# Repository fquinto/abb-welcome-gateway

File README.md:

# abb-welcome-gateway

ESP32-S3 gateway that connects an **ABB-Welcome / Busch-Welcome** 2-wire door
intercom to **Home Assistant**: doorbell notifications, remote door opening and
diagnostics, powered directly from the intercom bus.

| Top | Bottom |
|---|---|
|  |  |

## Highlights

- **Bus-powered**: TPS5430 buck converter runs the board from the ~28 V bus.
- **ESP32-S3-WROOM-1** with the antenna at the board edge and a proper copper
  keep-out.
- **Clean bus front-end**: filtered tap, TVS + reverse-polarity protection,
  polyfuse, Schmitt-buffered RX and open-drain TX drivers.
- **Three separated ground islands** (power / digital / bus) stitched at a
  single star point, so switching and RF return currents stay out of the bus
  reference.
- **ESPHome firmware**: native Home Assistant integration, OTA updates,
  YAML-only configuration for the end user.

## Repository layout

| Path | Contents |
|---|---|
| [`hardware/kicad-v3/`](hardware/kicad-v3/) | **The board** (KiCad 9): fully routed 2-layer PCB, DRC-clean. Source of truth for the hardware. |
| [`firmware/esphome/`](firmware/esphome/) | ESPHome configuration + `abb_welcome` custom component. |
| [`docs/`](docs/) | [Status](docs/STATUS.md) · [Pending tasks](docs/TODO.md) · [User guide](docs/user-guide.md). |
| [`legacy/`](legacy/) | Frozen design history: original EasyEDA v2 design, the tscircuit schematic capture of v3 and the conversion tooling. |

## Status

- **Hardware**: v3.0 design finished and fully routed; pre-fabrication
  verification pending (details in [docs/STATUS.md](docs/STATUS.md)).
- **Firmware**: ESPHome skeleton in place; ABB-Welcome bus protocol in
  development ([docs/TODO.md](docs/TODO.md)).

## Getting started

See the [user guide](docs/user-guide.md) for wiring, first flash over the
FTDI header and Home Assistant setup.

For hardware development: open `hardware/kicad-v3/abb-welcome-gateway-v3.kicad_pro`
in KiCad 9. Design rules, net classes and the ground-island scheme are described
in [`hardware/kicad-v3/README.md`](hardware/kicad-v3/README.md).

## Community & discussion

Questions, ideas or want to share your build? Join the discussion on Telegram:

## Donations for software development

If this project is useful to you, you can support its development:

Thank you for collaborating and helping the development of software improvements.

## Credits & license

The hardware derives from the original bus interface design by **mat931**.
Hardware is licensed under **CERN-OHL-W v2** (see [`LICENSE`](LICENSE));
the full design history is preserved in [`legacy/`](legacy/) and in the git log.

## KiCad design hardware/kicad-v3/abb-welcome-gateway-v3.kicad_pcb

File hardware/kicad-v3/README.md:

# KiCad v3 — routing target

KiCad project exported from the tscircuit v3 design (`legacy/tscircuit/index.circuit.tsx`)
so the board can be **routed in KiCad** (tscircuit's autorouter does not converge
on this board and produces no copper pours, which this design needs — three GND
islands, an RF module, the buck power stage and the 28 V bus all want planes /
poured copper, not point-to-point traces).

## Files

- `abb-welcome-gateway-v3.kicad_pro` — project (open this in KiCad).
- `abb-welcome-gateway-v3.kicad_pcb` — board: **fully routed** (traces, vias,
  the three GND island pours and stitching). `kicad-cli pcb drc`: 0 errors,
  0 unconnected items.
- `abb-welcome-gateway-v3.kicad_sch` — schematic.

Generated with `circuit-json-to-kicad` (KiCad file format `20241229`, i.e. KiCad 8/9).

## Source-of-truth note

Routing has started (and finished) here, so **this KiCad project is now the
source of truth for the PCB**. The tscircuit side (`legacy/tscircuit/index.circuit.tsx`)
is frozen as schematic reference; it does NOT reflect the physical changes below.

### Divergences from the tscircuit source (v3.0 routed)

- **U2 footprint replaced**: the tscircuit wrapper's hand-made 61-pad QFN-style
  footprint is not the real module. U2 now uses KiCad's official
  `RF_Module:ESP32-S3-WROOM-1` (41 pads + EP), antenna flush with the top board
  edge, with its copper keep-out.
- **LED_PIN moved from GPIO2 to GPIO6** (module pin 38 -> pin 6): the status
  LED net could not be routed out of the P2/FTDI quadrant. **Firmware must
  drive the status LED on GPIO6, not GPIO2.**
- **Board grown to 45.4 x 56.4 mm** (+3 mm height) to fit the buck band.
- Placement reworked by ground island (DGND top / BUS_GND middle+bus entry /
  PGND bottom): U1 rotated 180 (VIN toward C7/C8, SW toward D1/L2), feedback
  divider at the FB pin, star point (R_PGND/R_BGND/R_DGND) bottom-right,
  C4/C6 moved into the PGND island, LEDs rotated 180 (cathodes west), R5 and
  R8 relocated, TVS1 next to C23.
- Several nets use short B.Cu jogs; the DGND plane keeps deliberate bridges
  (module strip, east region) — re-run the zone fill after any edit.

## Regenerating (before any manual routing)

The export is driven by `@tscircuit/eval` → `circuit-json-to-kicad`. On a machine
where the tscircuit CLI runs (it needs the platform-native `@resvg/resvg-js`
binary), the supported one-liner is:

```bash
cd output
npx tsci export -f kicad_pcb index.circuit.tsx     # or: -f kicad_zip for the whole project
```

(These files were produced via the library path because the CLI's resvg binary
wasn't available in the generating environment; `tsci export` is the canonical way.)

## Routing checklist for this board

- Pour **separate ground regions** for `PGND` / `DGND` / `BUS_GND`; tie them only at
  the star point via R_PGND / R_DGND / R_BGND (the 0 Ω links).
- Keep the ESP32-S3 **antenna keep-out** clear (no copper under/near the antenna).
- Wide traces / short loops on the **buck power stage** (BUS_PWR, SW_NODE, PGND, L2, C2).
- **HV clearance** on the 28 V bus front-end (P1, F2, L1, D2/D4/D5/D7, TVS1).

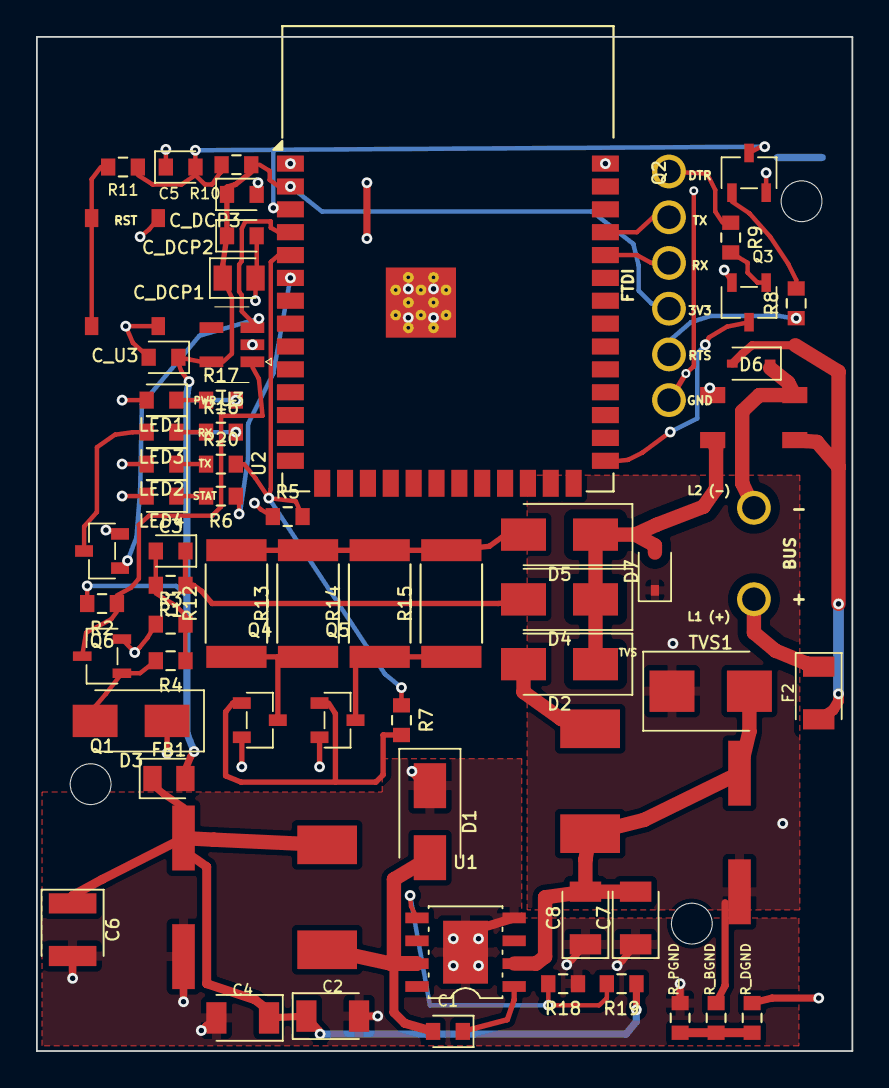
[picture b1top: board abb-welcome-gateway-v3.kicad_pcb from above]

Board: 2 copper layers, 45.3 x 56.3 mm, 66 parts (0 on the bottom side), 40 nets.

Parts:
C1: 10nF; 0603B103K500NT
C2, C4: 10uF; TAJA106K016RNJ
C3: 68nF; CL10B683KB8NNNC
C5: 100nF; CC0603KRX7R9BB104
C6: 100uF; TAJB107K006RNJ
C7, C8: 2.2uF; CL31B225KBHNNNE
C19: RVT470UF16V67RV0031
C23: VEJ101M1HTR-0810
C_DCP1: 22uF; capacitor_0805
C_DCP2: 1uF; capacitor_0603
C_DCP3: 100nF; capacitor_0603
C_U3: 100nF; capacitor_0603
D1, D2, D3, D4, D5: D; SS24
D6, D7: D; SD36C
F2: F2; fuse
FB1: 0H; inductor_0805
L1: ACT45B-510-2P-TL003
L2, L3: SMMS0650-101M
LED1: KT-0603R
LED2, LED3: 19-213_Y2C-CQ2R2L_3T
LED4: 19-217_BHC-ZL1M2RY_3T
P1: WJ500V-5.08-2P
P2: 61300611121; PinHeader_1x06_2.54mm
Q1, Q2, Q3: S8050
Q4, Q5, Q6: 2N7002
R1, R8, R9: 100kΩ; resistor_res0603
R2, R3, R10: 10kΩ; resistor_res0603
R4, R5, R6, R17: 1kΩ; resistor_res0603
R7: 75Ω; resistor_res0603
R11, R16, R20: 150Ω; resistor_res0603
R12, R13, R14, R15: 820Ω; FRC2512F8200TS
R18: 3.3kΩ; resistor_res0603
R19: 5.6kΩ; resistor_res0603
R_BGND: 0Ω; resistor_res0603
R_DGND: 0Ω; resistor_res0603
R_PGND: 0Ω; resistor_res0603
SW1: TS-1187A-B-A-B
TVS1: D; SMBJ30A
U1: TPS5430DDAR
U2: ESP32-S3-WROOM-1-N16R8; ESP32-S3-WROOM-1
U3: SN74LVC1G14DBVR; SOT-23-5

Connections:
BOOT_CAP: C1.1, U1.1
BOOT_STRAP: Q3.3, U2.27
BUS_DC_RAW: D2.2, L3.1
BUS_FUSED: D6.2, F2.2, L1.1
BUS_GND: C23.2, D3.1, D7.1, L1.3, Q1.2, Q4.2, Q5.2, Q6.2, R3.1, R_BGND.1, TVS1.1
BUS_HOT: F2.1, P1.2
BUS_HOT_F: D2.1, D4.1, D5.1, D7.2, L1.4
BUS_PWR: C7.2, C8.2, C23.1, L3.2, TVS1.2, U1.2
BUS_RTN: D6.1, L1.2, P1.1
BUS_RX_A: C3.1, D4.2, R1.1
BUS_RX_BIAS: D3.2, Q1.1, R4.2
BUS_RX_DET: Q1.3, R2.1, U3.1
BUS_RX_FILT: C3.2, R1.2, R3.2, R4.1
BUS_RX_PIN: Q6.1, U2.4, U3.3
BUS_TX: D5.2, R12.2, R13.2, R14.2, R15.2
BUS_TX_PIN: R5.2, R7.1, R20.2, U2.5
D0_DRIVE: Q3.1, R9.2
DGND: C5.1, C_DCP1.2, C_DCP2.2, C_DCP3.2, C_U3.2, LED1.2, LED2.2, LED4.2, P2.1, Q2.2, Q3.2, R5.1, R_DGND.1, SW1.3, SW1.4, U2.1, U2.40, U2.41, U3.2
DTR: P2.6, R9.1
EN: C5.2, Q2.3, R10.1, R11.2, U2.3
EN_DRIVE: Q2.1, R8.2
FB_TAP: R18.2, R19.2, U1.5
GND: R_BGND.2, R_DGND.2, R_PGND.2
LED_PIN: R6.2, U2.6
PGND: C2.2, C4.2, C6.2, C7.1, C8.1, C19.2, D1.1, R18.1, R_PGND.1, U1.4, U1.9
PWR_LED_A: LED1.1, R17.1
RST_BTN: R11.1, SW1.1, SW1.2
RTS: P2.2, R8.1
RX: P2.4, U2.36
RX_LED_A: LED3.1, R16.1
RX_LED_K: LED3.2, Q6.3
STAT_LED_A: LED4.1, R6.1
SW_NODE: C1.2, D1.2, L2.1, U1.7
TX: P2.5, U2.37
TX_DRAIN_A: Q4.3, R12.1, R13.1
TX_DRAIN_B: Q5.3, R14.1, R15.1
TX_GATE: Q4.1, Q5.1, R7.2
TX_LED_A: LED2.1, R20.1
V3V3: C2.1, C4.1, C6.1, C19.1, FB1.1, L2.2, R19.1
V3V3_ESP: C_DCP1.1, C_DCP2.1, C_DCP3.1, C_U3.1, FB1.2, P2.3, R2.2, R10.2, R16.2, R17.2, U2.2, U3.5

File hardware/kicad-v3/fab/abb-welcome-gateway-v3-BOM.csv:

Designator,Qty,Value,Footprint,Manufacturer Part,LCSC
C1,1,10nF,0603B103K500NT,0603B103K500NT,C57112
"C2,C4",2,10uF,TAJA106K016RNJ,TAJA106K016RNJ,C7171
C3,1,68nF,CL10B683KB8NNNC,CL10B683KB8NNNC,C31658
C5,1,100nF,CC0603KRX7R9BB104,CC0603KRX7R9BB104,C14663
C6,1,100uF,TAJB107K006RNJ,TAJB107K006RNJ,C16133
"C7,C8",2,2.2uF,CL31B225KBHNNNE,CL31B225KBHNNNE,C50254
C19,1,RVT470UF16V67RV0031,RVT470UF16V67RV0031,RVT470UF16V67RV0031,C2858857
C23,1,VEJ101M1HTR-0810,VEJ101M1HTR-0810,VEJ101M1HTR-0810,C176665
C_DCP1,1,22uF,capacitor_0805,22uF,
C_DCP2,1,1uF,capacitor_0603,1uF,
"C_DCP3,C_U3",2,100nF,capacitor_0603,100nF,
"D1,D2,D3,D4,D5",5,D,SS24,SS24,C7420362
"D6,D7",2,D,SD36C,SD36C,C502537
F2,1,F2,fuse,nSMD005,C70064
FB1,1,0H,inductor_0805,BLM21AG601SN1D,
L1,1,ACT45B-510-2P-TL003,ACT45B-510-2P-TL003,ACT45B-510-2P-TL003,C76584
"L2,L3",2,SMMS0650-101M,SMMS0650-101M,SMMS0650-101M,C2894722
LED1,1,KT-0603R,KT-0603R,KT-0603R,C2286
"LED2,LED3",2,19-213_Y2C-CQ2R2L_3T,19-213_Y2C-CQ2R2L_3T,19-213_Y2C-CQ2R2L_3T,C72038
LED4,1,19-217_BHC-ZL1M2RY_3T,19-217_BHC-ZL1M2RY_3T,19-217_BHC-ZL1M2RY_3T,C72041
P1,1,WJ500V-5.08-2P,WJ500V-5.08-2P,WJ500V-5.08-2P,C8465
P2,1,61300611121,PinHeader_1x06_2.54mm,61300611121,
"Q1,Q2,Q3",3,S8050,S8050,S8050,C2146
"Q4,Q5,Q6",3,2N7002,2N7002,2N7002,C8545
"R1,R8,R9",3,100kΩ,resistor_res0603,100kΩ,
"R2,R3,R10",3,10kΩ,resistor_res0603,10kΩ,
"R4,R5,R6,R17",4,1kΩ,resistor_res0603,1kΩ,
R7,1,75Ω,resistor_res0603,75Ω,
"R11,R16,R20",3,150Ω,resistor_res0603,150Ω,
"R12,R13,R14,R15",4,820Ω,FRC2512F8200TS,FRC2512F8200TS,C2999541
R18,1,3.3kΩ,resistor_res0603,3.3kΩ,
R19,1,5.6kΩ,resistor_res0603,5.6kΩ,
"R_BGND,R_DGND,R_PGND",3,0Ω,resistor_res0603,0Ω,
SW1,1,TS-1187A-B-A-B,TS-1187A-B-A-B,TS-1187A-B-A-B,C318884
TVS1,1,D,SMBJ30A,SMBJ30A,C699005
U1,1,TPS5430DDAR,TPS5430DDAR,TPS5430DDAR,C9864
U2,1,ESP32-S3-WROOM-1-N16R8,ESP32-S3-WROOM-1,ESP32-S3-WROOM-1-N16R8,C5736265
U3,1,SN74LVC1G14DBVR,SOT-23-5,SN74LVC1G14DBVR,

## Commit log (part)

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2026-05-17 Improvements
2026-06-13 Evolucion del diseno: ESP32-S3-WROOM-1, nuevos imports y generador de chips
    - output/: migracion a ESP32-S3-WROOM-1, buffer Schmitt, islas de GND
    (PGND/DGND/BUS_GND), bead + desacoplo en 3V3, terminacion de bus
    - nuevos imports: ESP32_S3_WROOM_1, MOSFET_2N7002, BJT_S8050; ajustes en TPS5430
    - tools/generate-import.mjs: generador de wrappers de chip
    - README: estado de diseno y revision pendiente antes de fabricacion
    - samples/ y configs actualizados
2026-06-13 Arreglo del front-end de RX, F2 como fuse y reorganizacion del repo
    - RX: separar BUS_RX_A (nodo de ~bus) de BUS_RX_DET (salida colector de Q1
    con pull-up R2 a V3V3_ESP). La entrada del Schmitt 74LVC1G14 ya no cuelga
    del nodo de alta tension; queda dentro de su abs-max (VCC+0.5V)
    - F2 polyfuse modelado como <fuse> en vez de <chip> (currentRating no era
    prop valida de chip; tsc --noEmit ahora pasa limpio)
    - mover fuente EasyEDA v2 + circuit.json a hardware/easyeda-v2/; repuntar
2026-06-13 Actualizar README: estado real v3.0 y tension de bus para TVS1
    - reescribir 'Known issues': los bugs de conectividad v2.x ya estan
    arreglados; documentar lo que queda
    - TVS1: el bus ABB-Welcome es 28V +-2V (controlador 28VDC), asi que
    SMBJ24CA (standoff 24V) conduce en operacion normal -> usar SMBJ30A,
    con la nota del compromiso clamp 48V vs abs-max 36V del TPS5430
    - mover RX/TX/divisor/F2/R_TERM/SW1 a la seccion 'Fixed in v3.0'
2026-06-13 TVS1 a SMBJ30A, pin de versiones, check de nets colgantes y CI
    - TVS1: SMBJ24CA -> SMBJ30A (unidireccional, catodo a BUS_PWR). El bus es
    28V +-2V, asi que el standoff de 24V conducia en operacion normal
    - output/package.json: pinear circuit-json 0.0.425 y tscircuit 0.0.1747
    (estaban en 'latest')
    - tools/check-dangling-nets.mjs: detecta nets con un solo pin en
    index.circuit.tsx; 'npm run check' y encadenado en 'npm run validate'
2026-06-13 CI: subir checkout/setup-node a v5 (Node 24)
2026-06-13 README: verificacion de L2 contra el datasheet del TPS5430
    100uH esta dentro del rango 10-100uH del datasheet (SLVS632L), pero con
    ~590uF de bulk el cruce del lazo (~1.5kHz) cae por debajo de la ventana
    3-30kHz de TI: estable pero lento, apoyado en la ESR del bulk. Avisos:
    no cambiar a ceramicos sin red de compensacion externa; alternativa
    L=15uH/100-220uF para cruce de libro
2026-06-13 Proceso: versionar package-lock y usar npm ci en CI
    - dejar de ignorar output/package-lock.json y versionarlo (regenerado con
    las versiones pineadas) para instalaciones reproducibles
    - CI: npm ci en vez de npm install (deterministico, mas rapido)
    - README: lock+npm ci movido a 'tooling in place'; snapshots quedan
    pendientes (necesitan binario nativo de resvg, mejor en la maquina dev)
2026-06-13 ESP32_S3_WROOM_1: schPinArrangement para esquematico legible
    Coloca solo los 9 pines que usa la placa (V3V3/EN arriba, GND abajo,
    RXD0/GPIO4 a la izquierda, TXD0/GPIO5/GPIO2/GPIO0 a la derecha) en vez de
    los 61. El resto siguen como puertos para el PCB. Verificado con
    @tscircuit/eval headless: el simbolo pasa de 61 a 9 puertos; tsc limpio.
    README: schPinArrangement marcado como hecho; anotado el
    pcb_autorouting_error visto durante el eval como pendiente de proceso.
2026-06-13 Export v3 a KiCad para rutear (hardware/kicad-v3/)
    El autorouter de tscircuit no converge en esta placa (sin terminar a 100x)
    y no hace pours, que este diseño necesita (islas GND, RF, potencia, bus HV).
    Se exporta el diseño v3 a KiCad via circuit-json-to-kicad:
    - .kicad_pcb: 66 footprints colocados, 218 pads, 200 nets, contorno; sin
    pistas (a rutear en KiCad)
    - .kicad_sch (216 simbolos) y .kicad_pro
